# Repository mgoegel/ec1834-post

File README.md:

# Robotron EC1834 POST 60h (and not only port 60) ISA card

Anleitung in [Deutsch](README-DE.md)

In this project I would like to introduce you to an ISA Port 60h card for the EC1834.

This project was inspired by:
https://bbright.tripod.com/information/postcard.htm
and by the ELV 1995-04 ISA-BIOS-POST Karte

## Description

### Decoding
The board uses 2 EPROMS for decoding the bus byte to the two 7 segment LED displays.
There may be better ways to do it (BCD to 7seg hex encoder or PAL ICs). Both techniques are obsolete and not/hardly available (as the used 2732/27C32 EPROMs are).
But to keep it as simple as possible, the EPROMs are the solution.

### Configuration
To support 74LS series ICs (the 74LS688), I used only pull up mechanisms for the configuration.
So the address lines NOT wanted, have to be switched **ON** at the DIP switch 
(which is - by the way - prepared to be replaced by a 2x10 PIN header),
when the address is to be defined.
For jumpers - these have to be set then.

Example:

* Adress 0x80 - Lines A0-A6,A8-A9 need to be set to **ON**; A7 to **OFF**
* Adress 0x60 - Lines A0-A4,A7-A9 must be **ON**; A5,A6 have to be **OFF**

The address range is configurable from 0x000-0x3ff

The display can be configured, to display read requests, instead of write requests. The Jumper J3 needs to be set to "Read".
Default should be "Write".

### Connectors
The board has 2 feature connectors.
The power connector J4 shall to be used later for a power monitoring. It provides access to all voltage (+5V, -5V, +12V, -12V, GND) lines on the ISA BUS.

Connector J2 provides easy access for a Logic analyzer. The bus data presents read and write access to IO ports on the configured port.
The ongoing transaction can be monitored on the /IOR or /IOW line, which is active low, depending on the bus transaction.

J0 can be installed as a DIN41612 64pin (a+c) connector, as no access to the 16bit data bus is needed.

## BOM

| Ref | Value               |
|-----|---------------------|
| C1  | 100n                |
| C2  | 100n                |
| C3  | 100n                |
| C4  | 100n                |
| C5  | 100n                |
| C6  | 100n                |
| C7  | 100uF               |
| C8  | 100n                |
| J0  | DIN 41612C 64(a+c) or 96 pin (abc) <br />female 90° THT connector  |
| J2  | Conn_02x07_Odd_Even |
| J3  | Conn_01x03          |
| J4  | Conn_02x06_Odd_Even |
| Q1  | BC337               |
| Q2  | BC337               |
| R1  | 2K2                 |
| R2  | 10k                 |
| R3  | 10k                 |
| R4  | 1k                  |
| R5  | 1k                  |
| R6  | 220                 |
| RN1 | SIL9-8 10K          |
| RN2 | SIL5-4 1,5K or 4x1,5K R |
| RN3 | SIL5-4 1,5K or 4x1,5K R |
| RN4 | SIL5-4 1,5K or 4x1,5K R |
| RN5 | SIL5-4 1,5K or 4x1,5K R |
| SW1 | SW_DIP_x10          |
| U1  | 74LS688             |
| U2  | 74LS86              |
| U3  | 7432                |
| U4  | 74HC374             |
| U5  | 2732                |
| U6  | 2732                |
| U7  | SA39-11EWA          |
| U8  | SA39-11EWA          |
| U9  | 74HC374             |

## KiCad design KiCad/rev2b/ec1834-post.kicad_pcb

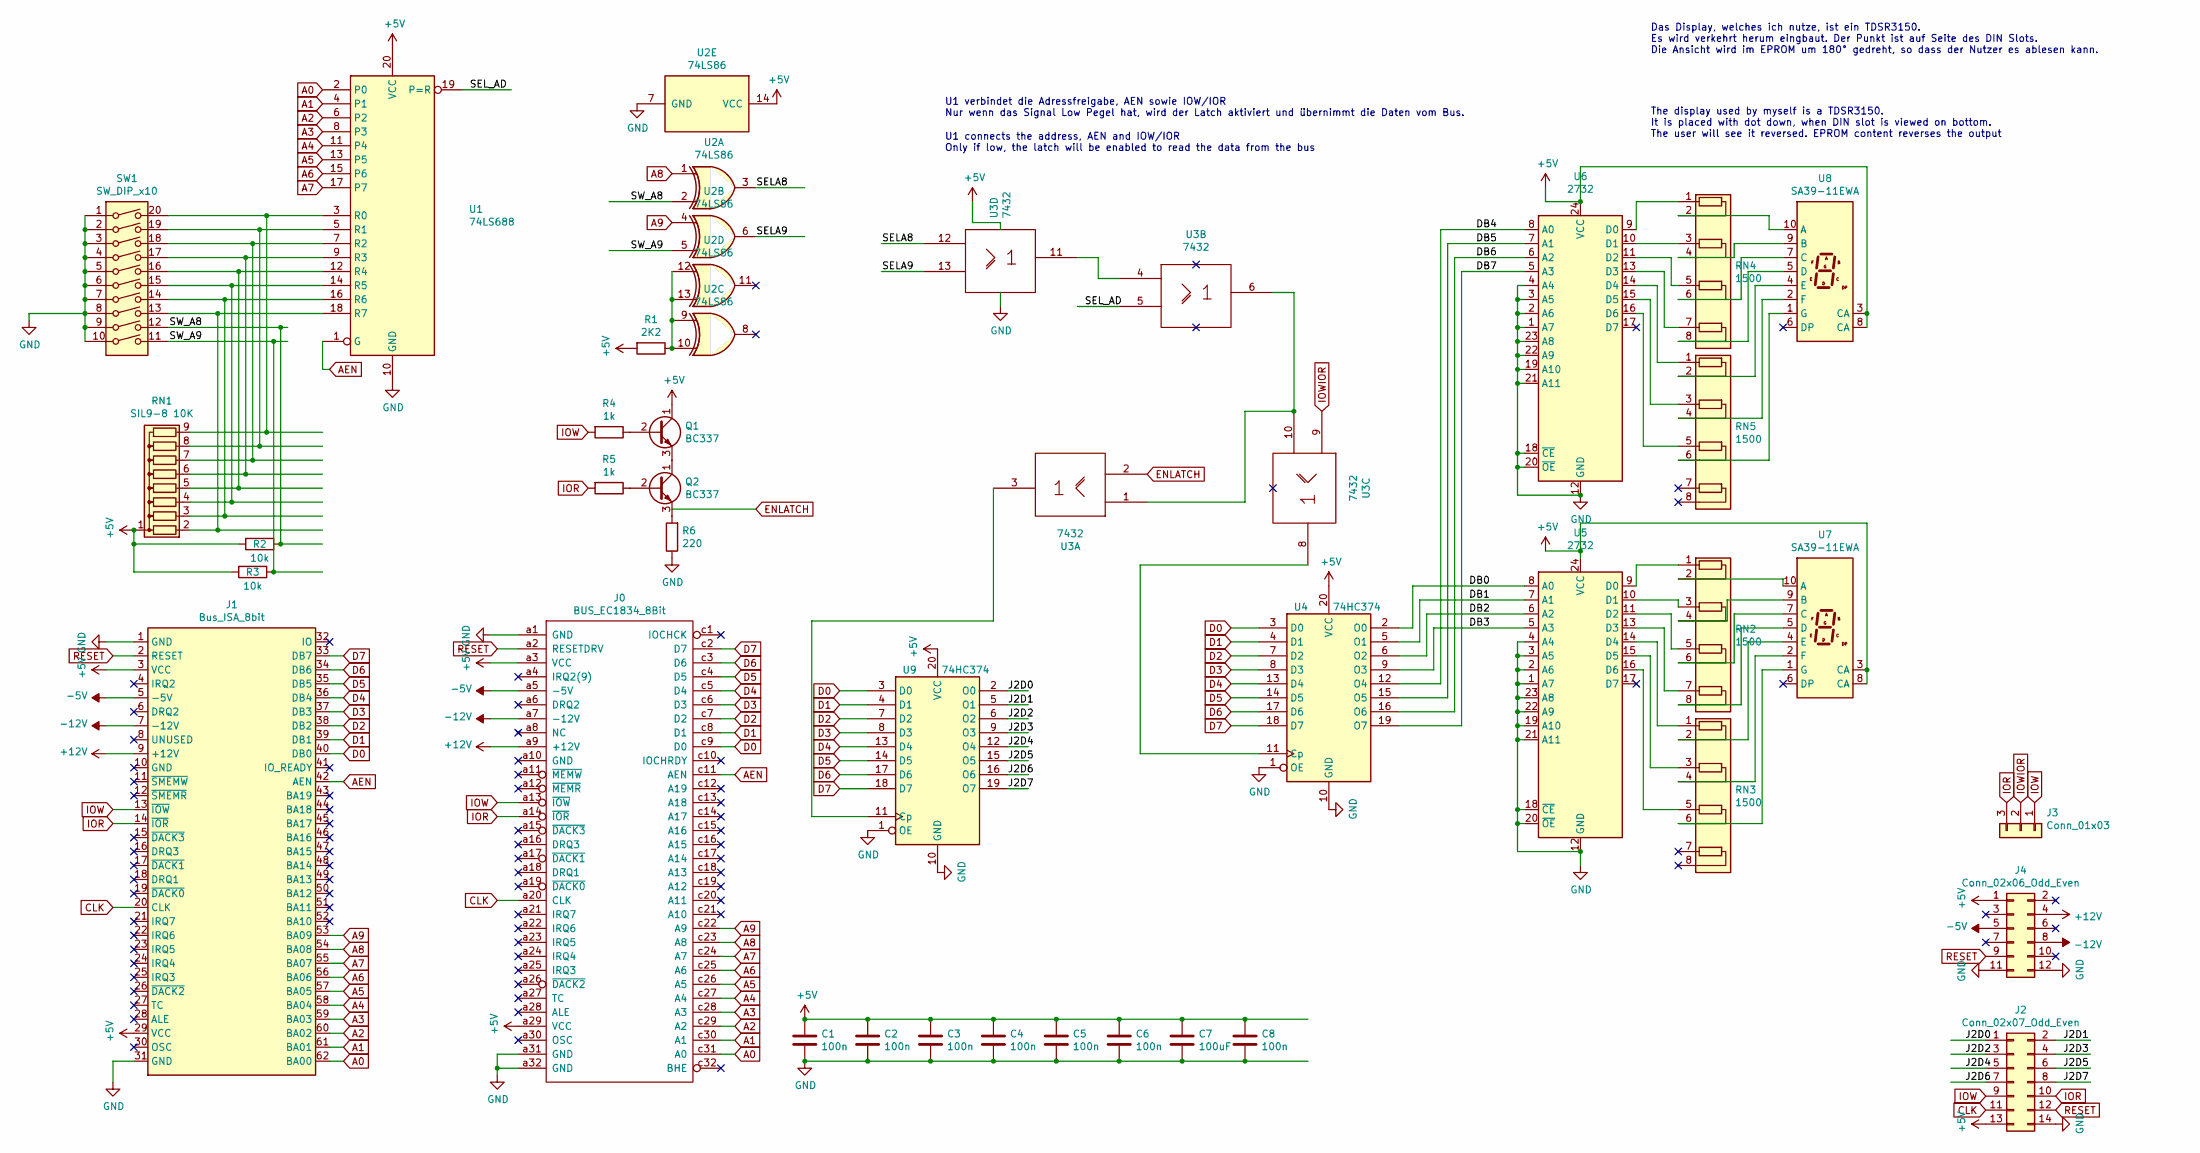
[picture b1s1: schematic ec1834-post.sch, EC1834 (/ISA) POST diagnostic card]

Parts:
C1, C2, C3, C4, C5, C6, C8: 100n; C_Axial_L3.8mm_D2.6mm_P7.50mm_Horizontal
C7: 100uF; CP_Radial_D6.3mm_P2.50mm
J0: BUS_EC1834_8Bit; DIN41612_C_3x32_Male_Horizontal_THT
J1: Bus_ISA_8bit; ISA-8BIT-XT-IDE
J2: Conn_02x07_Odd_Even; PinHeader_2x07_P2.54mm_Vertical
J3: Conn_01x03; PinHeader_1x03_P2.54mm_Vertical
J4: Conn_02x06_Odd_Even; PinHeader_2x06_P2.54mm_Vertical
Q1, Q2: BC337; TO-92_Inline
R1: 2K2; R_Axial_DIN0207_L6.3mm_D2.5mm_P10.16mm_Horizontal
R2, R3: 10k; R_Axial_DIN0207_L6.3mm_D2.5mm_P10.16mm_Horizontal
R4, R5: 1k; R_Axial_DIN0207_L6.3mm_D2.5mm_P10.16mm_Horizontal
R6: 220; R_Axial_DIN0207_L6.3mm_D2.5mm_P10.16mm_Horizontal
RN1: SIL9-8 10K; R_Array_SIP9
RN2, RN3, RN4, RN5: 1500; R_Array_SIP8
SW1: SW_DIP_x10; SW_DIP_SPSTx10_Slide_9.78x27.58mm_W7.62mm_P2.54mm
U1: 74LS688; DIP-20_W7.62mm
U2: 74LS86; DIP-14_W7.62mm
U3: 7432; DIP-14_W7.62mm
U4, U9: 74HC374; DIP-20_W7.62mm
U5, U6: 2732; DIP-24_W15.24mm
U7, U8: SA39-11EWA; Sx39-1xxxxx

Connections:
+5V: C1.1, C2.1, C3.1, C4.1, C5.1, C6.1, C7.1, C8.1, J0.a3 (VCC), J0.a29 (VCC), J1.3 (VCC), J1.29 (VCC), J2.13, J4.1, Q1.1 (C), R1.2, R2.2, R3.2, RN1.1 (common), U1.20 (VCC), U2.14 (VCC), U3.14 (Vcc), U4.20 (VCC), U5.24 (VCC), U6.24 (VCC), U7.3 (CA), U7.8 (CA), U8.3 (CA), U8.8 (CA), U9.20 (VCC)
+12V: J0.a9 (+12V), J1.9 (+12V), J4.4
-5V: J0.a5 (-5V), J1.5 (-5V), J4.5
-12V: J0.a7 (-12V), J1.7 (-12V), J4.8
/DB0: U4.2 (O0), U5.8 (A0)
/DB1: U4.5 (O1), U5.7 (A1)
/DB2: U4.6 (O2), U5.6 (A2)
/DB3: U4.9 (O3), U5.5 (A3)
/DB4: U4.12 (O4), U6.8 (A0)
/DB5: U4.15 (O5), U6.7 (A1)
/DB6: U4.16 (O6), U6.6 (A2)
/DB7: U4.19 (O7), U6.5 (A3)
/J2D0: J2.1, U9.2 (O0)
/J2D1: J2.2, U9.5 (O1)
/J2D2: J2.3, U9.6 (O2)
/J2D3: J2.4, U9.9 (O3)
/J2D4: J2.5, U9.12 (O4)
/J2D5: J2.6, U9.15 (O5)
/J2D6: J2.7, U9.16 (O6)
/J2D7: J2.8, U9.19 (O7)
/SELA8: U2.3, U3.12
/SELA9: U2.6, U3.13
/SEL_AD: U1.19 (P=R), U3.5
/SW_A8: R2.1, SW1.12, U2.2
/SW_A9: R3.1, SW1.11, U2.5
A0: J0.c31 (A0), J1.62 (BA00), U1.2 (P0)
A1: J0.c30 (A1), J1.61 (BA01), U1.4 (P1)
A2: J0.c29 (A2), J1.60 (BA02), U1.6 (P2)
A3: J0.c28 (A3), J1.59 (BA03), U1.8 (P3)
A4: J0.c27 (A4), J1.58 (BA04), U1.11 (P4)
A5: J0.c26 (A5), J1.57 (BA05), U1.13 (P5)
A6: J0.c25 (A6), J1.56 (BA06), U1.15 (P6)
A7: J0.c24 (A7), J1.55 (BA07), U1.17 (P7)
A8: J0.c23 (A8), J1.54 (BA08), U2.1
A9: J0.c22 (A9), J1.53 (BA09), U2.4
AEN: J0.c11 (AEN), J1.42 (AEN), U1.1 (G)
CLK: J0.a20 (CLK), J1.20 (CLK), J2.11
D0: J0.c9 (D0), J1.40 (DB0), U4.3 (D0), U9.3 (D0)
D1: J0.c8 (D1), J1.39 (DB1), U4.4 (D1), U9.4 (D1)
D2: J0.c7 (D2), J1.38 (DB2), U4.7 (D2), U9.7 (D2)
D3: J0.c6 (D3), J1.37 (DB3), U4.8 (D3), U9.8 (D3)
D4: J0.c5 (D4), J1.36 (DB4), U4.13 (D4), U9.13 (D4)
D5: J0.c4 (D5), J1.35 (DB5), U4.14 (D5), U9.14 (D5)
D6: J0.c3 (D6), J1.34 (DB6), U4.17 (D6), U9.17 (D6)
D7: J0.c2 (D7), J1.33 (DB7), U4.18 (D7), U9.18 (D7)
ENLATCH: U3.2
GND: C1.2, C2.2, C3.2, C4.2, C5.2, C6.2, C7.2, C8.2, J0.a1 (GND), J0.a31 (GND), J0.a32 (GND), J1.1 (GND), J1.31 (GND), J2.14, J4.11, J4.12, R6.1, SW1.1, SW1.2, SW1.3, SW1.4, SW1.5, SW1.6, SW1.7, SW1.8, SW1.9, SW1.10, U1.10 (GND), U2.7 (GND), U3.7 (Gnd), U4.1 (OE), U4.10 (GND), U5.1 (A7), U5.2 (A6), U5.3 (A5), U5.4 (A4), U5.12 (GND), U5.18 (~CE), U5.19 (A10), U5.20 (~OE), U5.21 (A11), U5.22 (A9), U5.23 (A8), U6.1 (A7), U6.2 (A6), U6.3 (A5), U6.4 (A4), U6.12 (GND), U6.18 (~CE), U6.19 (A10), U6.20 (~OE), U6.21 (A11), U6.22 (A9), U6.23 (A8), U9.1 (OE), U9.10 (GND); also elsewhere on the board
IOR: J0.a14 (~IOR), J1.14 (~IOR), J2.10, J3.3, R5.2
IOW: J0.a13 (~IOW), J1.13 (~IOW), J2.9, J3.1, R4.2
IOWIOR: J3.2, U3.9
unnamed: Q1.2 (B), R4.1
unnamed: Q1.3 (E), Q2.1 (C)
unnamed: Q2.2 (B), R5.1
unnamed: Q2.3 (E), R6.2
unnamed: R1.1, U2.9, U2.10, U2.12, U2.13
unnamed: RN1.2 (R1), SW1.13, U1.18 (R7)
unnamed: RN1.3 (R2), SW1.14, U1.16 (R6)
unnamed: RN1.4 (R3), SW1.15, U1.14 (R5)
unnamed: RN1.5 (R4), SW1.16, U1.12 (R4)
unnamed: RN1.6 (R5), SW1.17, U1.9 (R3)
unnamed: RN1.7 (R6), SW1.18, U1.7 (R2)
unnamed: RN1.8 (R7), SW1.19, U1.5 (R1)
unnamed: RN1.9 (R8), SW1.20, U1.3 (R0)
unnamed: RN2.1 (R1.1), U5.9 (D0)
unnamed: RN2.2 (R1.2), U7.10 (A)
unnamed: RN2.3 (R2.1), U5.10 (D1)
unnamed: RN2.4 (R2.2), U7.9 (B)
unnamed: RN2.5 (R3.1), U5.11 (D2)
unnamed: RN2.6 (R3.2), U7.7 (C)
unnamed: RN2.7 (R4.1), U5.13 (D3)
unnamed: RN2.8 (R4.2), U7.5 (D)
unnamed: RN3.1 (R1.1), U5.14 (D4)
unnamed: RN3.2 (R1.2), U7.4 (E)
unnamed: RN3.3 (R2.1), U5.15 (D5)
unnamed: RN3.4 (R2.2), U7.2 (F)
unnamed: RN3.5 (R3.1), U5.16 (D6)
unnamed: RN3.6 (R3.2), U7.1 (G)
unnamed: RN4.1 (R1.1), U6.9 (D0)
unnamed: RN4.2 (R1.2), U8.10 (A)
unnamed: RN4.3 (R2.1), U6.10 (D1)
unnamed: RN4.4 (R2.2), U8.9 (B)
unnamed: RN4.5 (R3.1), U6.11 (D2)
unnamed: RN4.6 (R3.2), U8.7 (C)
unnamed: RN4.7 (R4.1), U6.13 (D3)
unnamed: RN4.8 (R4.2), U8.5 (D)
unnamed: RN5.1 (R1.1), U6.14 (D4)
unnamed: RN5.2 (R1.2), U8.4 (E)
unnamed: RN5.3 (R2.1), U6.15 (D5)
unnamed: RN5.4 (R2.2), U8.2 (F)
unnamed: RN5.5 (R3.1), U6.16 (D6)
unnamed: RN5.6 (R3.2), U8.1 (G)
unnamed: U3.1, U3.6, U3.10
unnamed: U3.3, U9.11 (Cp)
unnamed: U3.8, U4.11 (Cp)
unnamed: U3.4, U3.11
RESET: J0.a2 (RESETDRV), J1.2 (RESET), J2.12, J4.9

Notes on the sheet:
U1 connects the address, AEN and IOW/IOR Only if low, the latch will be enabled to read the data from the bus
The display used by myself is a TDSR3150. It is placed with dot down, when DIN slot is viewed on bottom. The user will see it reversed. EPROM content reverses the output
Das Display, welches ich nutze, ist ein TDSR3150. Es wird verkehrt herum eingbaut. Der Punkt ist auf Seite des DIN Slots. Die Ansicht wird im EPROM um 180° gedreht, so dass der Nutzer es ablesen kann.
U1 verbindet die Adressfreigabe, AEN sowie IOW/IOR Nur wenn das Signal Low Pegel hat, wird der Latch aktiviert und übernimmt die Daten vom Bus.

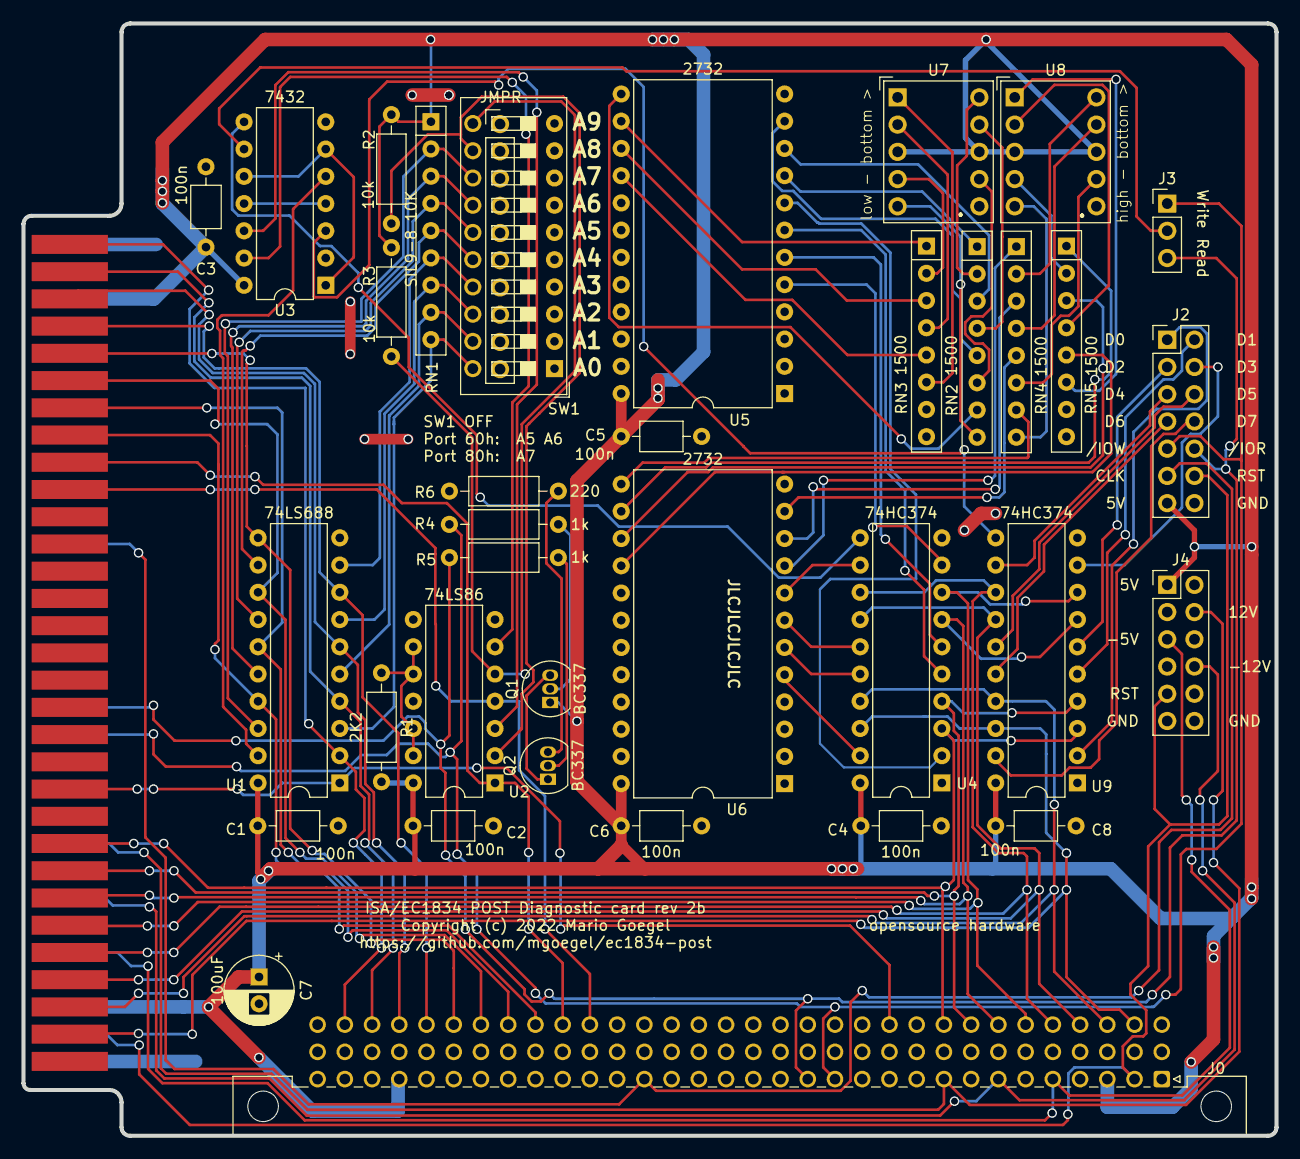
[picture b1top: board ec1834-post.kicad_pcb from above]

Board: 2 copper layers, 116.9 x 103.7 mm, 37 parts (0 on the bottom side), 95 nets.

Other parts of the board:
JMPR: JMPR; PinHeader_1x10_P2.54mm_Vertical

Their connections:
GND: JMPR.1, JMPR.2, JMPR.3, JMPR.4, JMPR.5, JMPR.6, JMPR.7, JMPR.8, JMPR.9, JMPR.10; also elsewhere on the board

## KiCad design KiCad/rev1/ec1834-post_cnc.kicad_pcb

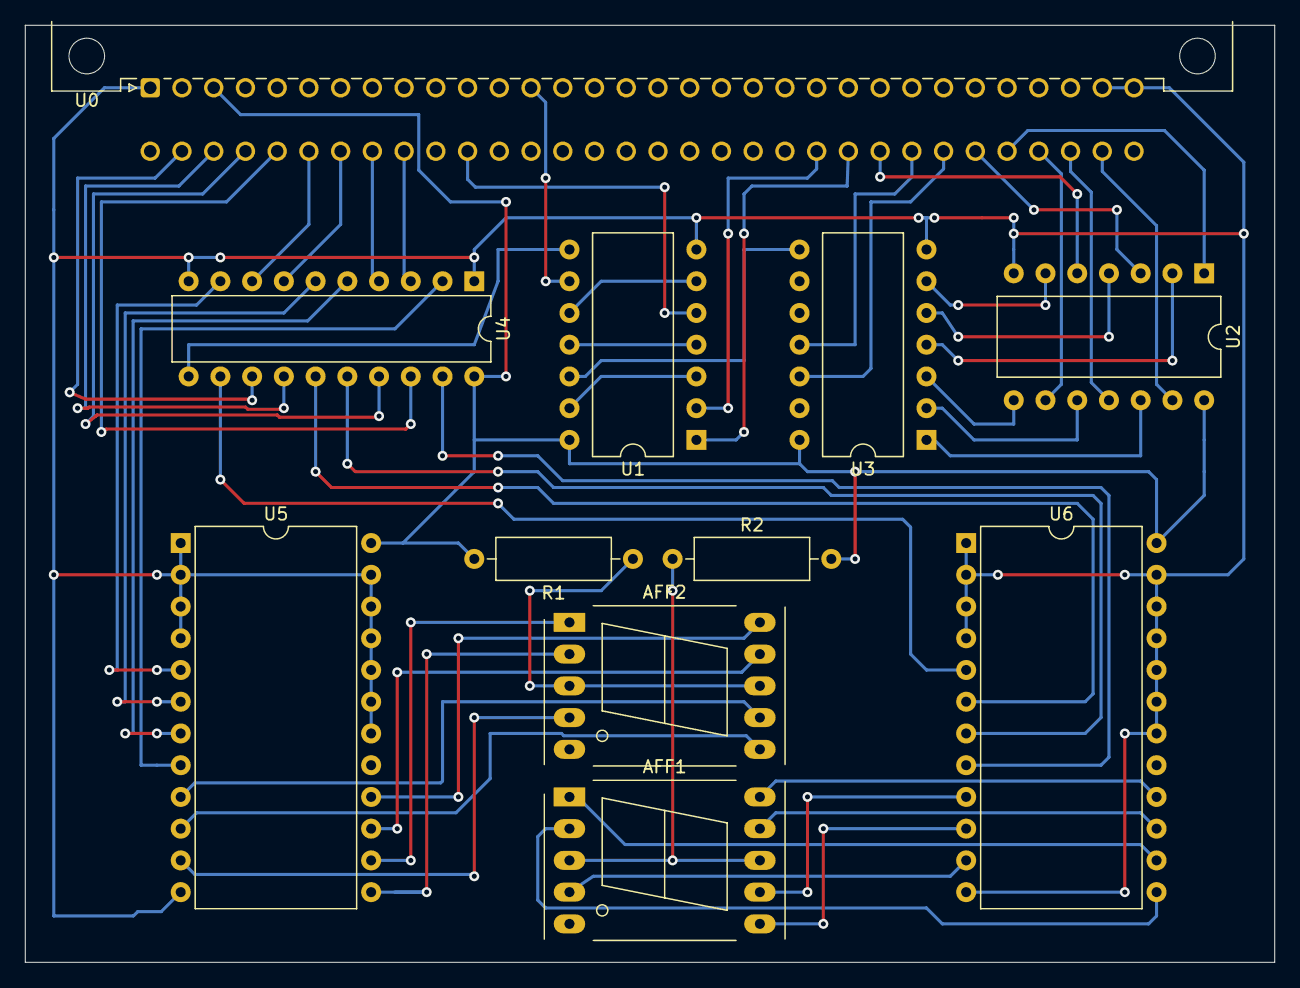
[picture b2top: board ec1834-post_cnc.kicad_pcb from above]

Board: 2 copper layers, 100.0 x 75.0 mm, 11 parts (0 on the bottom side), 57 nets.

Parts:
AFF1, AFF2: LTS-6960HR; 7SegmentLED_LTS6760_LTS6780
R1, R2: 470; R_Axial_DIN0309_L9.0mm_D3.2mm_P12.70mm_Horizontal
U0: BUS_EC1834_8Bit; DIN41612_C_2x32_Male_Horizontal_THT
U1: 7432; DIP-14_W10.16mm
U2: 74HC04; DIP-14_W10.16mm
U3: 7430; DIP-14_W10.16mm
U4: 74HC374; DIP-20_W7.62mm
U5, U6: 2732; DIP-24_W15.24mm

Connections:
+5V: R1.2, R2.2, U0.a3, U1.14, U2.14, U3.14, U4.20, U5.24, U6.24
A0: U0.c31, U2.13
A1: U0.c30, U2.11
A2: U0.c29, U2.9
A3: U0.c28, U2.1
A4: U0.c27, U2.3
A5: U0.c26, U3.12
A6: U0.c25, U3.11
A7: U0.c24, U2.5
A8: U0.c23, U1.1
A9: U0.c22, U1.2
AEN: U0.c11, U1.5
D0: U0.c9, U4.3
D1: U0.c8, U4.4
D2: U0.c7, U4.7
D3: U0.c6, U4.8
D4: U0.c5, U4.18
D5: U0.c4, U4.17
D6: U0.c3, U4.14
D7: U0.c2, U4.13
GND: U0.a1, U0.a31, U0.a32, U1.7, U2.7, U3.7, U4.1, U4.10, U5.1, U5.2, U5.3, U5.4, U5.12, U5.18, U5.19, U5.20, U5.21, U5.22, U5.23, U6.1, U6.2, U6.3, U6.4, U6.12, U6.18, U6.19, U6.20, U6.21, U6.22, U6.23
IOW: U0.a13, U1.9
unnamed: AFF1.1, U6.14
unnamed: AFF1.2, U6.13
unnamed: AFF1.3, AFF1.8, R2.1
unnamed: AFF1.4, U6.11
unnamed: AFF1.6, U6.10
unnamed: AFF1.7, U6.9
unnamed: AFF1.9, U6.15
unnamed: AFF1.10, U6.16
unnamed: AFF2.1, U5.14
unnamed: AFF2.2, U5.13
unnamed: AFF2.3, AFF2.8, R1.1
unnamed: AFF2.4, U5.11
unnamed: AFF2.6, U5.10
unnamed: AFF2.7, U5.9
unnamed: AFF2.9, U5.15
unnamed: AFF2.10, U5.16
unnamed: U1.8, U4.11
unnamed: U1.6, U1.10
unnamed: U1.4, U1.11
unnamed: U1.12, U3.8
unnamed: U1.3, U1.13
unnamed: U2.2, U3.4
unnamed: U2.4, U3.5
unnamed: U2.6, U3.6
unnamed: U2.8, U3.3
unnamed: U2.10, U3.2
unnamed: U2.12, U3.1
unnamed: U4.2, U5.8
unnamed: U4.5, U5.7
unnamed: U4.6, U5.6
unnamed: U4.9, U5.5
unnamed: U4.12, U6.5
unnamed: U4.15, U6.6
unnamed: U4.16, U6.7
unnamed: U4.19, U6.8

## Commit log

2022-03-20 Created EC1834 BUS symbol
2022-03-22 Schema completed Building PCB...
2022-04-03 Rework from CNC layout (which would be too close for 3018) to better layout for JLCPCB
2022-04-25 Added EPROM content Fixed DIP footprints (too wide) Added ISA BUS/Edge
2022-04-30 New revision routing still in progress
2022-05-03 Rebuild of PCB is done
2022-05-03 Updated schema, fixed wrong footprint
2022-05-03 Added 3d view
2022-05-04 reorganized directory
2022-05-04 Some cleanup in files
2022-06-03 Updated scheme to rev2 Update EPROM binaries Updated PCB to rev2 and new foot prints Added better documentation
2022-06-03 Fixed README headers
2022-06-03 Another README fix
2022-06-20 Some schematics beautify actions Added schematics as PNG Typo fixed in BOM
2022-06-21 Fixed schematics and PCB (RN2-RN5 value changed to 1K5 R) Added an image Added german documentation
2022-06-21 Bugfix in READMEs
2022-06-21 typo in german README

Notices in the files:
KiCad/rev2b/ec1834-post.kicad_pcb:
Copyright (c) 2022 Mario Goegel
